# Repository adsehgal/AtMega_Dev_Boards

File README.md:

# Custom AtMega Development Boards
### Aditya Sehgal

</p>This repo is a compilation of custom development boards I have taken upon myself to design. These boards house the AtMega family of microcontrollers and are similar to Arduino boards, however, with personal customizations as follows:</p>
 <il>   

- Reduce the physical size of the reference Arduinos by roughly half.
- Implement USB-C for future proofing.
- Remove unnecessary components.
 <il>
<br>

</p>The gerber files can be sent to JLCPCB.com for manufacturing since they agree with their constraints and the components can be ordered via LCSC.com using the BOMs provided.<br>
Hand soldering the PCBs may come across as a bit of a challenge for some since it requires parctice with QFP packages as well as 3225 packaged crystal oscillators with pads on the bottom. Both of these are easily solderable if you have access to a hot air station, but definitely doable with a temperature controlled iron and a well tip.<br>
The BOMs can be simply uploaded to LCSC using their BOM tool to add all required components directly to cart. Note to be made here, header pins are not included in the BOM since I want to leave the choice of male/female up to the designer.</p>

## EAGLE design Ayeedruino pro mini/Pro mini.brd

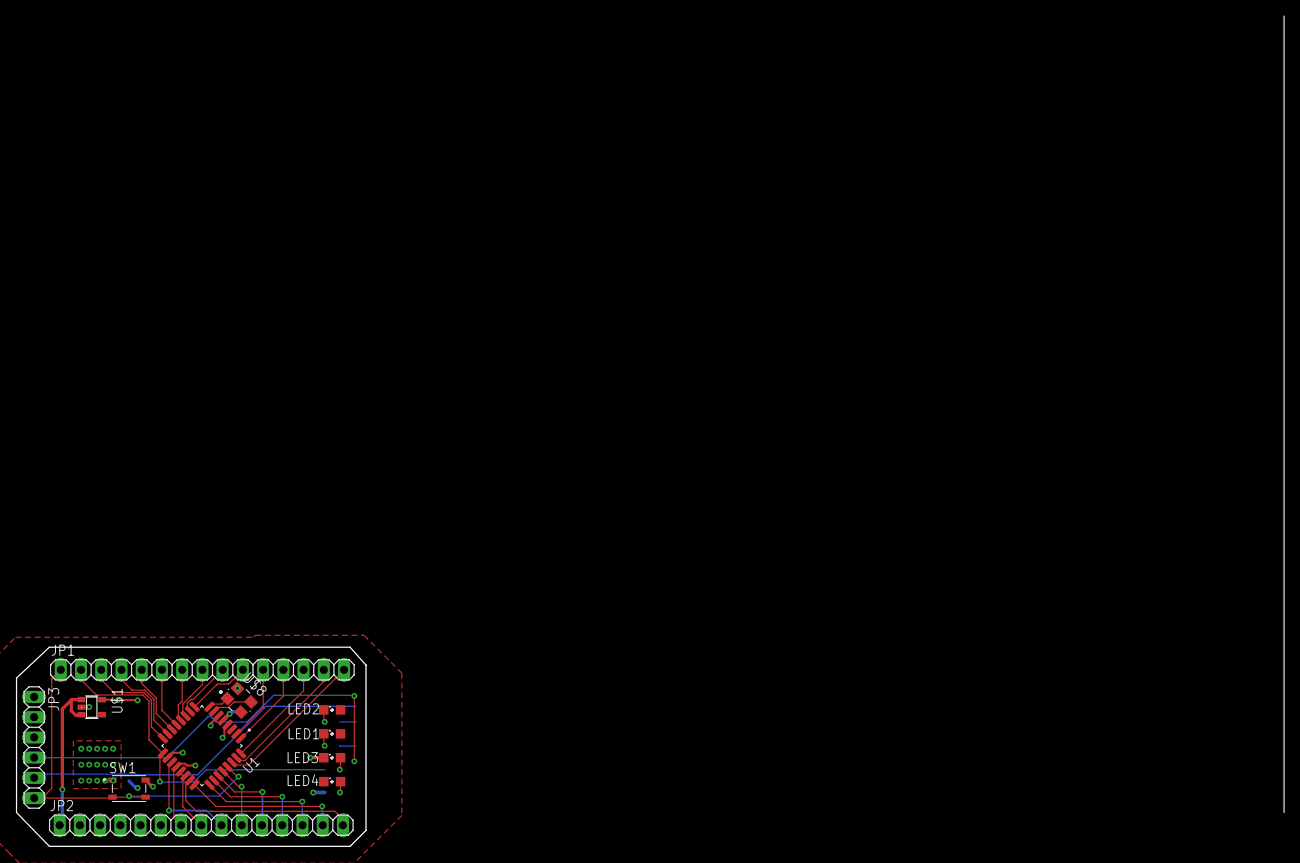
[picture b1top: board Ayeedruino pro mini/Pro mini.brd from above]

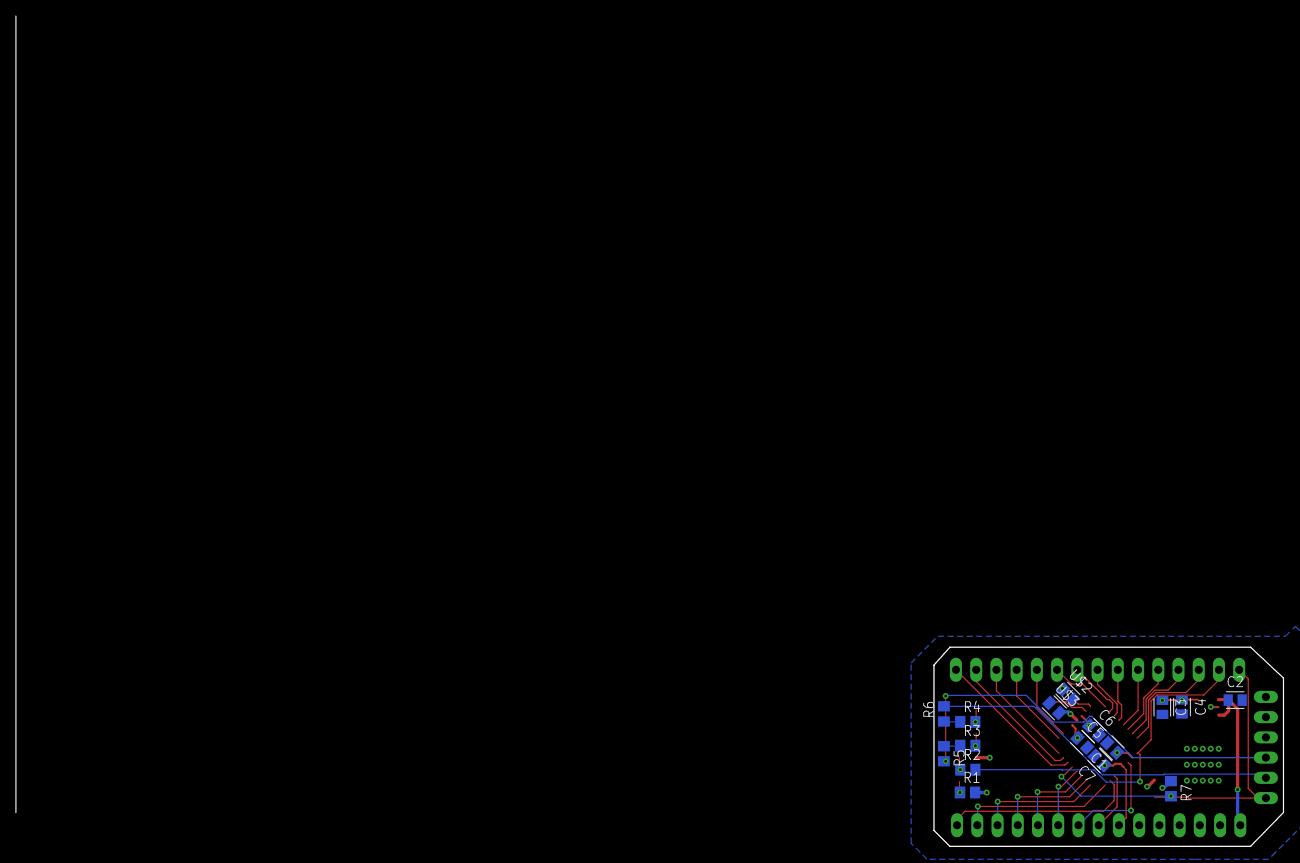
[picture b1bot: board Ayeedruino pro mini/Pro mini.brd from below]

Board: 2 copper layers, 43.9 x 25.0 mm, 27 parts (16 on the bottom side), 37 nets.

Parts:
C1, C2, C3, C4, C5, C6, C7: CAPC2012X110
JP1, JP2: 1X15
JP3: 1X06
LED1, LED2, LED4: SML0805
LED3: D13; SML0805
R1, R2, R3, R4, R5, R6, R7: R0805
SW1: PTS810_SJM_250_SMTR_LFS; SW_PTS810_SJM_250_SMTR_LFS
U1: ATMEGA328P-AU; TQFP-32
U$1: MIC5205SOT23-5; SOT23-5
U$2, U$3: CAPC2012X110
U$8: OSCCC320X250X60

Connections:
+5V: C1.1, C3.1, C4.1, C5.1, C6.1, JP2.2, JP2.3, JP3.3, LED1.A, LED2.A, R1.2, R7.1, U1.4, U1.6, U1.18, U$1.5
A0: JP2.15, U1.23
A1: JP2.14, U1.24
A2: JP2.13, U1.25
A3: JP2.12, U1.26
A4: JP2.11, U1.27
A5: JP2.10, U1.28
A6: JP2.9, U1.19
A7: JP2.8, U1.22
AREF: C7.1, JP2.7, U1.20
D0: JP1.15, U1.30
D1: JP1.14, U1.31
D2: JP1.13, U1.32
D3: JP1.12, U1.1
D4: JP1.11, U1.2
D5: JP1.10, U1.9
D6: JP1.9, U1.10
D7: JP1.8, U1.11
D8: JP1.7, U1.12
D9: JP1.6, U1.13
D10: JP1.5, U1.14
D11: JP1.4, U1.15
D12: JP1.3, U1.16
D13: JP1.2, R2.2, U1.17
GND: C1.2, C2.2, C3.2, C4.2, C5.2, C6.2, C7.2, JP2.4, JP2.5, JP2.6, JP3.1, JP3.2, LED3.C, LED4.C, SW1.1, SW1.2, U1.3, U1.5, U1.21, U$1.2, U$2.1, U$3.2, U$8.2, U$8.4
unnamed: LED3.A, R2.1
unnamed: LED1.C, R3.2
unnamed: JP3.4, R5.2
unnamed: JP3.5, R6.2
unnamed: LED2.C, R4.2
unnamed: LED4.A, R1.1
OSC1: U1.8, U$2.2, U$8.1
OSC2: U1.7, U$3.1, U$8.3
RAW: C2.1, JP2.1, U$1.1, U$1.3
RST: JP1.1, JP3.6, R7.2, SW1.3, SW1.4, U1.29
RX: R3.1, R5.1
TX: R4.1, R6.1

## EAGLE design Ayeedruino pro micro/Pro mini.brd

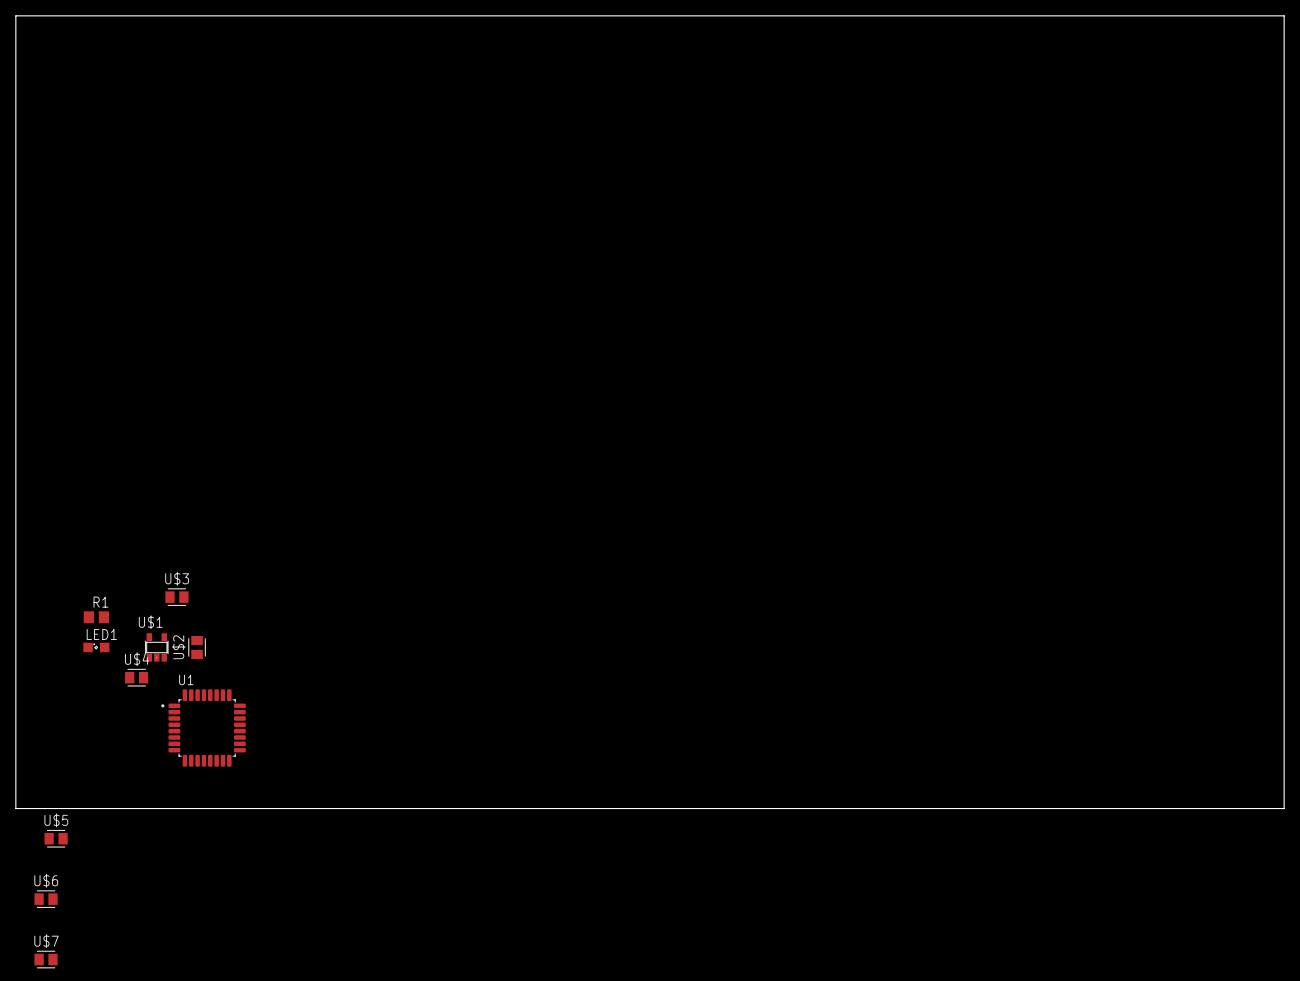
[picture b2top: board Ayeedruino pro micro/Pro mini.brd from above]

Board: 2 copper layers, 160.0 x 100.0 mm, 10 parts (0 on the bottom side), 5 nets, no tracks yet.

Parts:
LED1: PWR; SML0805
R1: R0805
U1: ATMEGA328P-AU; TQFP-32
U$1: MIC5205SOT23-5; SOT23-5
U$2, U$3: 10µF; CAPC2012X110
U$4, U$5, U$6, U$7: 0.1µF; CAPC2012X110

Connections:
+5V: R1.2, U1.4, U1.6, U1.18, U$1.5, U$3.1, U$4.1, U$5.1, U$6.1
GND: LED1.C, U1.3, U1.5, U1.21, U$1.2, U$2.2, U$3.2, U$4.2, U$5.2, U$6.2, U$7.2
unnamed: U1.20, U$7.1
unnamed: LED1.A, R1.1
RAW: U$1.1, U$1.3, U$2.1

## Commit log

2020-03-20 update - empty
2020-03-20 Removed kicad files
2020-03-20 updated gitignore
2020-03-20 ignore updated
2020-03-20 Repositioned reset button - added fourth mounting hole
2020-03-20 Schematic update
2020-03-20 readme update
2020-03-20 Update Uno
2020-03-20 Uno Updates
2020-03-20 Uno Gerber updated
2020-03-20 BOM added
2020-03-20 remove redudancies
2020-03-20 Upload pro mini start
2020-04-10 Repor readme updated
2020-06-26 Started New Aueeduino Uno with 328pb
2020-07-19 working on layout
2020-07-27 Macro_Keys Layout complete + Programmer WIP
2020-08-07 Merge-no major changes
2020-08-28 removed redundancies
